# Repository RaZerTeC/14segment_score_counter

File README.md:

## 14segment_score_counter

Punktezähler-Platine für Brett- und Kartenspiele: 0–99 hoch/runterzählbar, 9 V-Batteriebetrieb, Anzeige des aktuellen Scores über 2* 7-Segment Anzeigen. Kein Unterlauf, bei 99 automatischer Sprung auf 0. Zusätzlicher Button fürs Zurücksetzen auf 0.

Eine kompakte (70*80mm), batteriebetriebene Punktezähl-Platine für den perfekten Spieleabend.

Unter dem Ordner KiCad findet ihr die Projektdateien:

- **14segment_score_counter.kicad_pro**  
  Hauptprojektdatei von KiCad

- **14segment_score_counter.kicad_sch**  
  Schaltplan-Datei

- **14segment_score_counter.kicad_pcb**  
  Leiterplattenlayout

- **14segment_score_counter.ino**  
  Arduinoprogramm
    
- **Die Fertigungsdaten mit BOM**

## Features

* Zählbereich: 0–99
* Mit Einschaltschalter um Energie zu sparen
* Hoch- und Herunterzählen per jeweiligen Taster
* Automatischer Rücksprung auf 0, wenn 99 erreicht 
* Kein Unterlauf möglich 
* Betrieb mit 9-V-Batterie

## Aufbau & Verwendung

1. 9-V-Batterie anschließen
2. Einschalttaste auf ON
3. Up/Down-Taster auf der Platine nutzen, um den Punktestand anzupassen
4. Mit der Reset-Taste den Punktestand auf 0 zurücksetzen
5. Bei 99 springt der Zähler automatisch wieder auf 0
6. Bei 0 stoppt der Down-Taster 

Frontansicht der Platine:

Rückansicht der Platine

Top-Layer der Platine

## Ideen für Erweiterungen

* Speicherung des Punktestands im EEPROM -->Zurzeit wird der Punktestand bei Energieverlust zurückgesetzt
* Mehrstellige Anzeige (z. B. bis 999)
* Bluetooth-Integration für Punkte-Apps
* Gehäuse für die Platine

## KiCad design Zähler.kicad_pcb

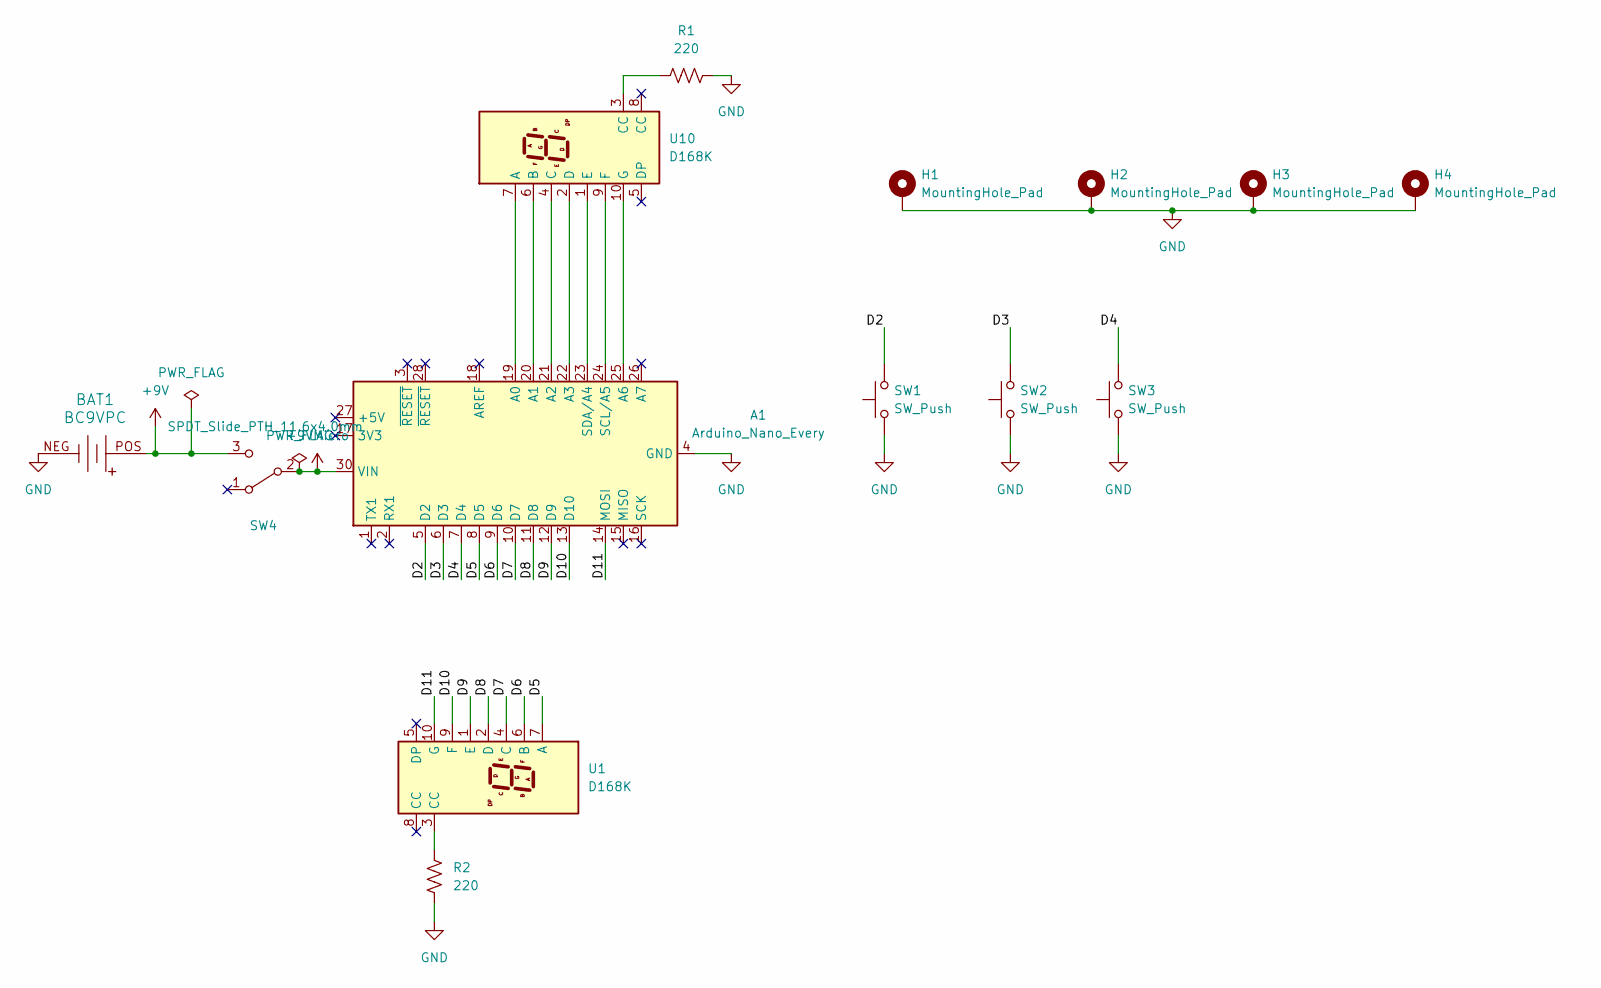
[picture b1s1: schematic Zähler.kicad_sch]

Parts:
A1: Arduino_Nano_Every; Arduino_Nano
BAT1: BC9VPC; Battery_Holder_9V_BC9VPC-ND; MPN BC9VPC; Digi-Key_PN BC9VPC-ND
H1, H2, H3, H4: MountingHole_Pad; MountingHole_3.2mm_M3_DIN965_Pad_TopBottom
R1, R2: 220; R_Axial_DIN0207_L6.3mm_D2.5mm_P7.62mm_Horizontal
SW1, SW2, SW3: SW_Push; SW_PUSH-12mm
SW4: SPDT_Slide_PTH_11.6x4.0mm; Slide_SPDT_PTH_11.6x4.0mm
U1, U10: D168K; D1X8K

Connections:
+9V: BAT1.POS, SW4.3 (C)
+9VMicro: A1.30 (VIN), SW4.2 (B)
/D2: A1.5 (D2), SW1.2
/D3: A1.6 (D3), SW2.2
/D4: A1.7 (D4), SW3.2
/D5: A1.8 (D5), U1.7 (A)
/D6: A1.9 (D6), U1.6 (B)
/D7: A1.10 (D7), U1.4 (C)
/D8: A1.11 (D8), U1.2 (D)
/D9: A1.12 (D9), U1.1 (E)
/D10: A1.13 (D10), U1.9 (F)
/D11: A1.14 (MOSI), U1.10 (G)
GND: A1.4 (GND), A1.29 (GND), BAT1.NEG, H1.1, H2.1, H3.1, H4.1, R1.1, R2.2, SW1.1, SW2.1, SW3.1
unnamed: A1.19 (A0), U10.7 (A)
unnamed: A1.20 (A1), U10.6 (B)
unnamed: A1.21 (A2), U10.4 (C)
unnamed: A1.22 (A3), U10.2 (D)
unnamed: A1.25 (A6), U10.10 (G)
unnamed: A1.24 (SCL/A5), U10.9 (F)
unnamed: A1.23 (SDA/A4), U10.1 (E)
unnamed: R1.2, U10.3 (CC)
unnamed: R2.1, U1.3 (CC)

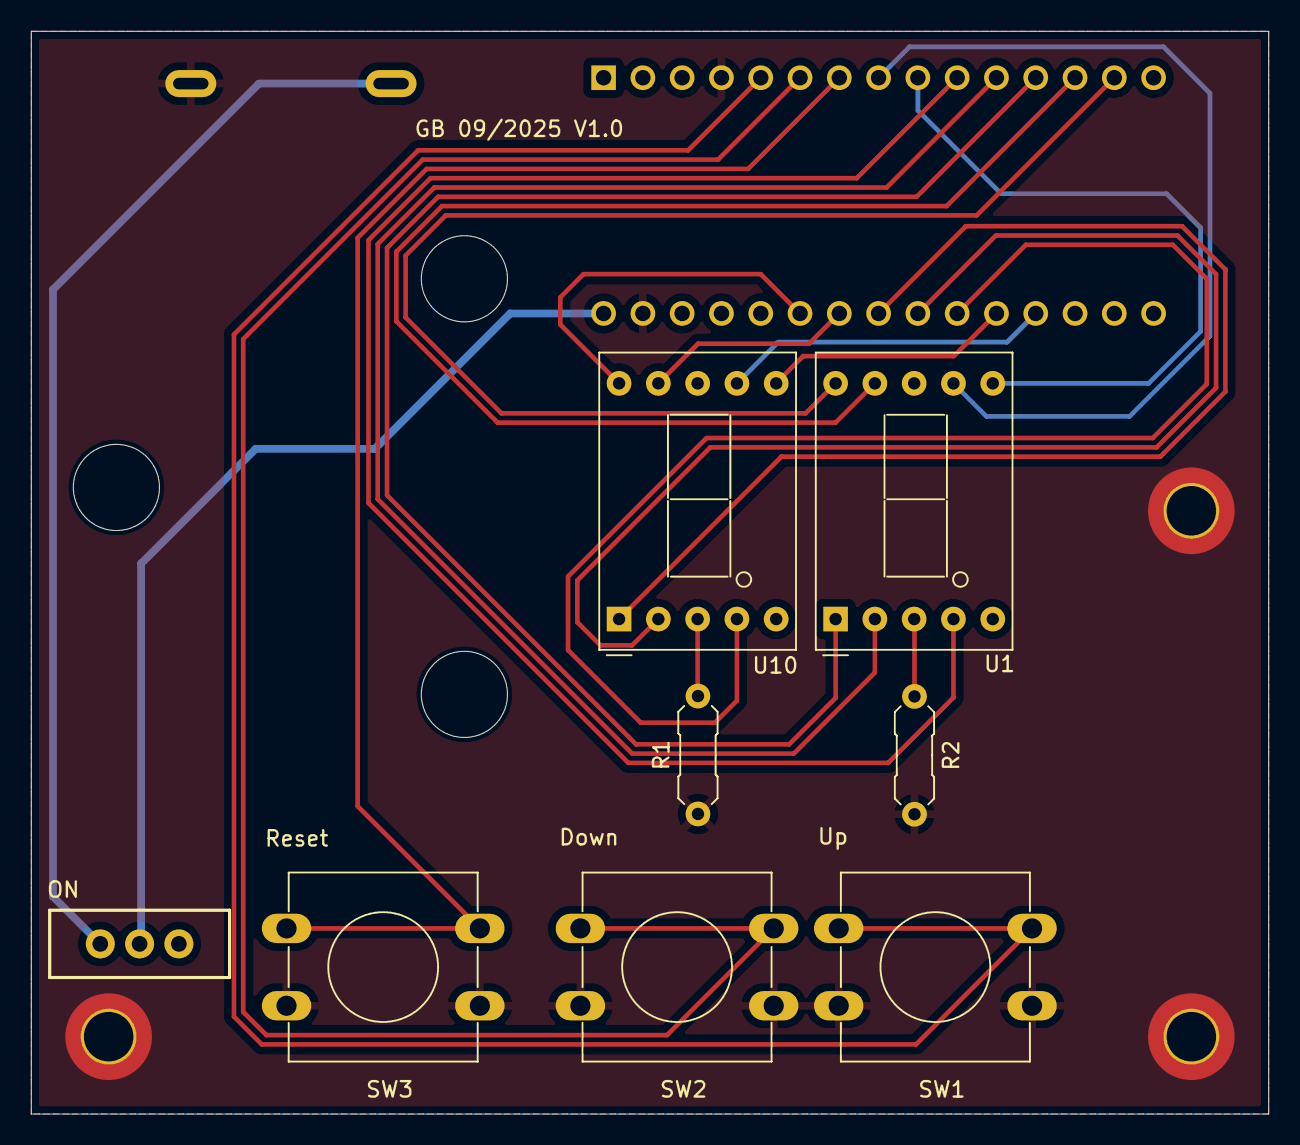
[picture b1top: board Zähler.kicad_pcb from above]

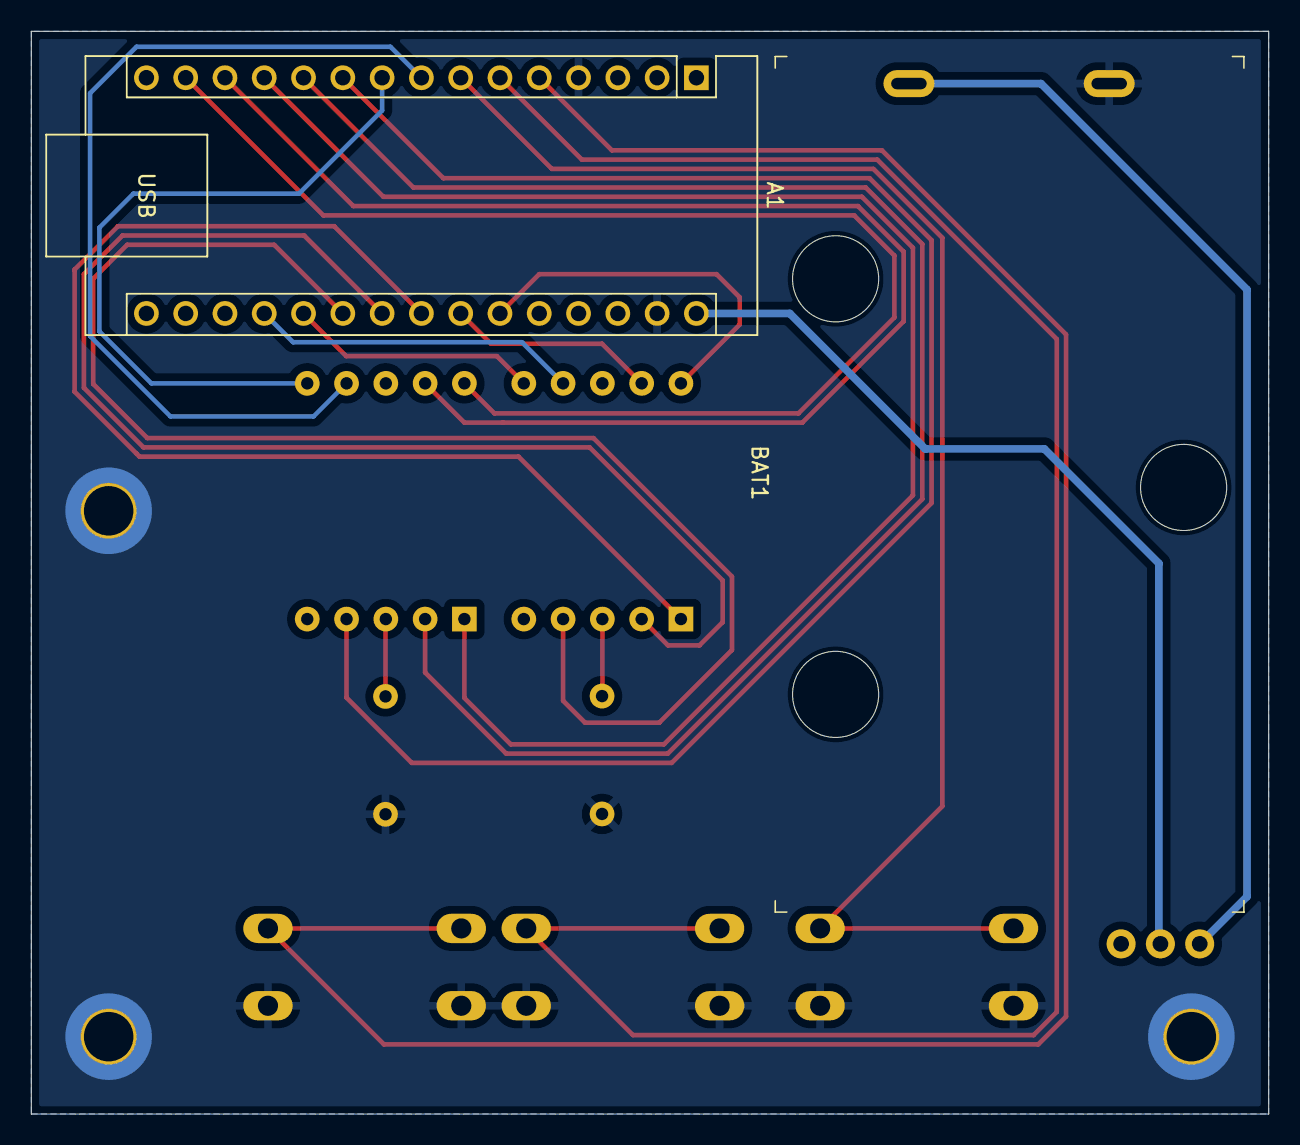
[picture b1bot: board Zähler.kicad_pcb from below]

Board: 2 copper layers, 80.0 x 70.0 mm, 13 parts (2 on the bottom side), 22 nets.

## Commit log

2025-11-18 Enhance README with features and usage details
    Added features, setup instructions, and expansion ideas.
2025-11-18 Projektdateien
2025-11-18 Update README with project files information
    Added project files section with descriptions for KiCad files.
2025-11-18 Renaming of file to 14segment_score_counter.kicad_pro file
2025-11-18 Rename 14segment_score_counter.kicad_pro to KiCadfiles/14segment_score_counter.kicad_pro
2025-11-18 Rename Zähler.kicad_pro to KiCadFiles/14segment_score_counter.kicad_pro
2025-11-18 Add 14segment_score_counter schematic file
2025-11-18 Add 14segment_score_counter-B_Cu.gbr file
2025-11-18 Rename Zähler-B_Mask.gbr to 14segment_score_counter-B_Mask.gbr
2025-11-18 Add 14segment_score_counter.csv to BOM directory
2025-11-18 Add 14segment_score_counter-NPTH.drl file
2025-11-18 Add 14segment_score_counter-PTH.drl file
2025-11-18 Rename Zähler-B_Paste.gbr to 14segment_score_counter-B_Paste.gbr
2025-11-18 Rename Zähler-B_Silkscreen.gbr to 14segment_score_counter-B_Silkscreen.gbr
2025-11-18 Rename Zähler-Edge_Cuts.gbr to 14segment_score_counter-Edge_Cuts.gbr
2025-11-18 Add 14segment_score_counter-F_Cu.gbr file
2025-11-18 Rename Zähler-F_Mask.gbr to 14segment_score_counter-F_Mask.gbr
2025-11-18 Add 14segment_score_counter-F_Paste.gbr file
2025-11-18 Add 14segment_score_counter-F_Silkscreen Gerber file
2025-11-18 Add top layer image of the PCB
    Added image of the top layer of the PCB to the README.
2025-11-18 Update README with project file names and features
2025-11-18 Fix typos in README features section
2025-11-18 Rename file to 14segment_score_counter.ino
2025-11-18 Update README to include Arduino program file
    Added Arduino program file to the README.
